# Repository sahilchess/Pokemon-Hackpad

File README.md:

# Pokemon Hackpad!
<!---

picture to come!
-->

[CAD](https://cad.onshape.com/documents/8d1a80880a531cce319d6767/w/a72820820093b362710dff01/e/ab70c80eedf68ce27917fcfd)

Pokemon Hackpad is a 5 key macropad with a rotary switch/encoder, and 4 SK6812 MINI E RGB LEDs. It uses KMK/QMK(wip) firmware. I designed this as my own macropad through [hackpad](https://hackclub.hackpad.com), a Hack Club program where you learn to design your own macropad and get it for free

## Features:
- An EC11 rotary encoder, controls volume, click to mute
- 3 SK6812 MINI E RGB LEDs, swirl and static modes
- 5 Cherry MX style keys
- 128x32 OLED Screen
- Pokemon themed design

## CAD Model:
Here is the case, made in onshape. I used onshape because Fusion basically blew my computer up. 

## PCB
Here's the PCB, made in KiCad.

## Firmware Overview
This hackpad uses [KMK](https://github.com/KMKfw/kmk_firmware) firmware for everything.
- the rotary encoder changes volume, press to mute
- the 5 regular keys are copy, paste, undo, redo
- rgb leds swirl by default, static color available

## BOM (more elaborate BOM [here](http://github.com/sahilchess/Pokemon-Hackpad/blob/main/production/BOM.md)):
Here should be everything you need to make this amazing hackpad
- 5x Cherry MX Switches
- 5x DSA Keycaps
- 6x 1N4148 DO-35 Diodes
- 3x SK6812 MINI E RGB LEDs
- 1x EC11 Rotary Encoder
- 1x 0.91 inch OLED display
- 4x M3x16mm screws
- 4x M3x5mx4mm heatset inserts
- 1x XIAO RP2040

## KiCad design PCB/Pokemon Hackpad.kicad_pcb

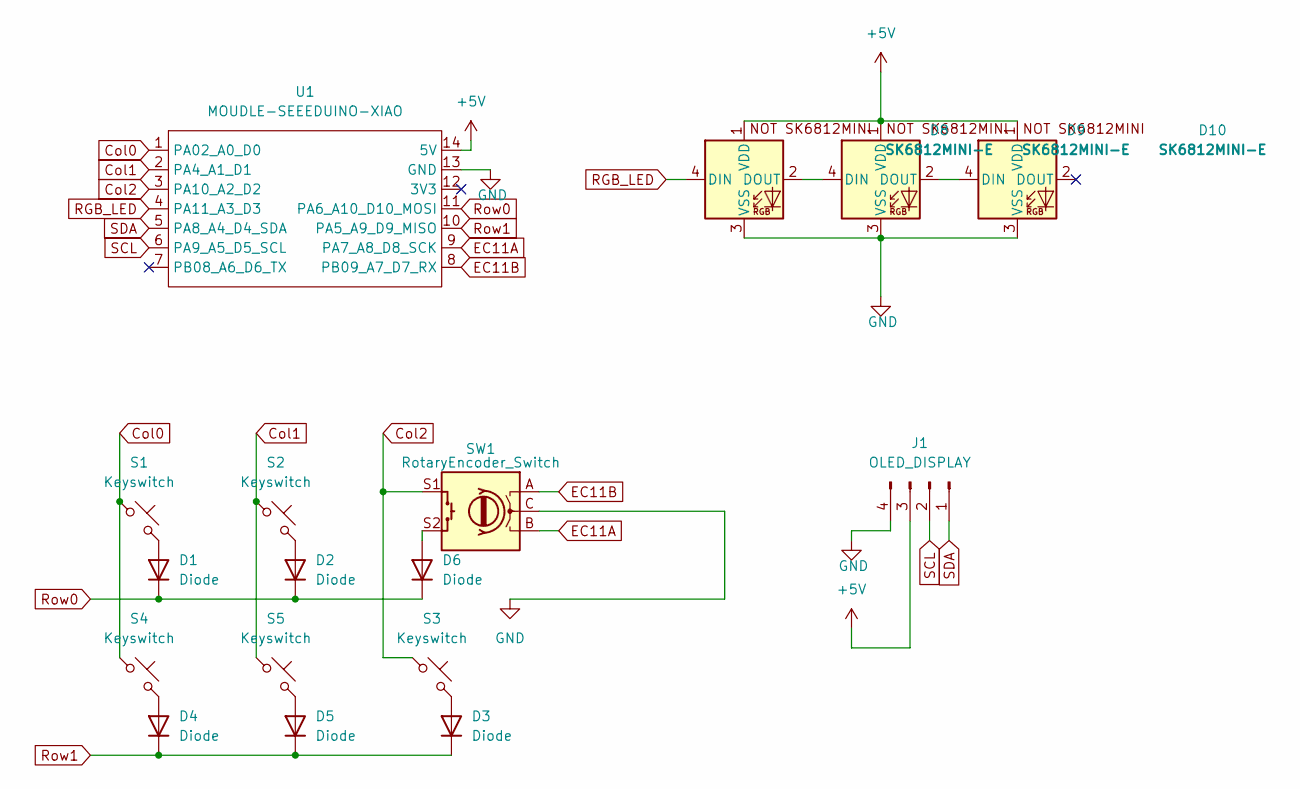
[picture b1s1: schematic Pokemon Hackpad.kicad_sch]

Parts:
D1, D2, D3, D4, D5, D6: Diode; D_DO-35_SOD27_P7.62mm_Horizontal
D8, D9, D10: SK6812MINI-E; LED_SK6812MINI-E_3.2x2.8mm_P1.5mm_ReverseMount
J1: OLED_DISPLAY; SSD1306-0.91-OLED-4pin-128x32
S1, S2, S3, S4, S5: Keyswitch; SW_Cherry_MX_1.00u_PCB
SW1: RotaryEncoder_Switch; RotaryEncoder_Alps_EC11E-Switch_Vertical_H20mm
U1: MOUDLE-SEEEDUINO-XIAO; XIAO-Generic-Hybrid-14P-2.54-21X17.8MM

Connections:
+5V: D8.1 (VDD), D9.1 (VDD), D10.1 (VDD), J1.3, U1.14 (5V)
Col0: S1.1, S4.1, U1.1 (PA02_A0_D0)
Col1: S2.1, S5.1, U1.2 (PA4_A1_D1)
Col2: S3.1, SW1.S1, U1.3 (PA10_A2_D2)
EC11A: SW1.B, U1.9 (PA7_A8_D8_SCK)
EC11B: SW1.A, U1.8 (PB09_A7_D7_RX)
GND: D8.3 (VSS), D9.3 (VSS), D10.3 (VSS), J1.4, SW1.C, U1.13 (GND)
unnamed: D1.2 (A), S1.2
unnamed: D2.2 (A), S2.2
unnamed: D3.2 (A), S3.2
unnamed: D4.2 (A), S4.2
unnamed: D5.2 (A), S5.2
unnamed: D6.2 (A), SW1.S2
unnamed: D8.2 (DOUT), D9.4 (DIN)
unnamed: D9.2 (DOUT), D10.4 (DIN)
RGB_LED: D8.4 (DIN), U1.4 (PA11_A3_D3)
Row0: D1.1 (K), D2.1 (K), D6.1 (K), U1.11 (PA6_A10_D10_MOSI)
Row1: D3.1 (K), D4.1 (K), D5.1 (K), U1.10 (PA5_A9_D9_MISO)
SCL: J1.2, U1.6 (PA9_A5_D5_SCL)
SDA: J1.1, U1.5 (PA8_A4_D4_SDA)

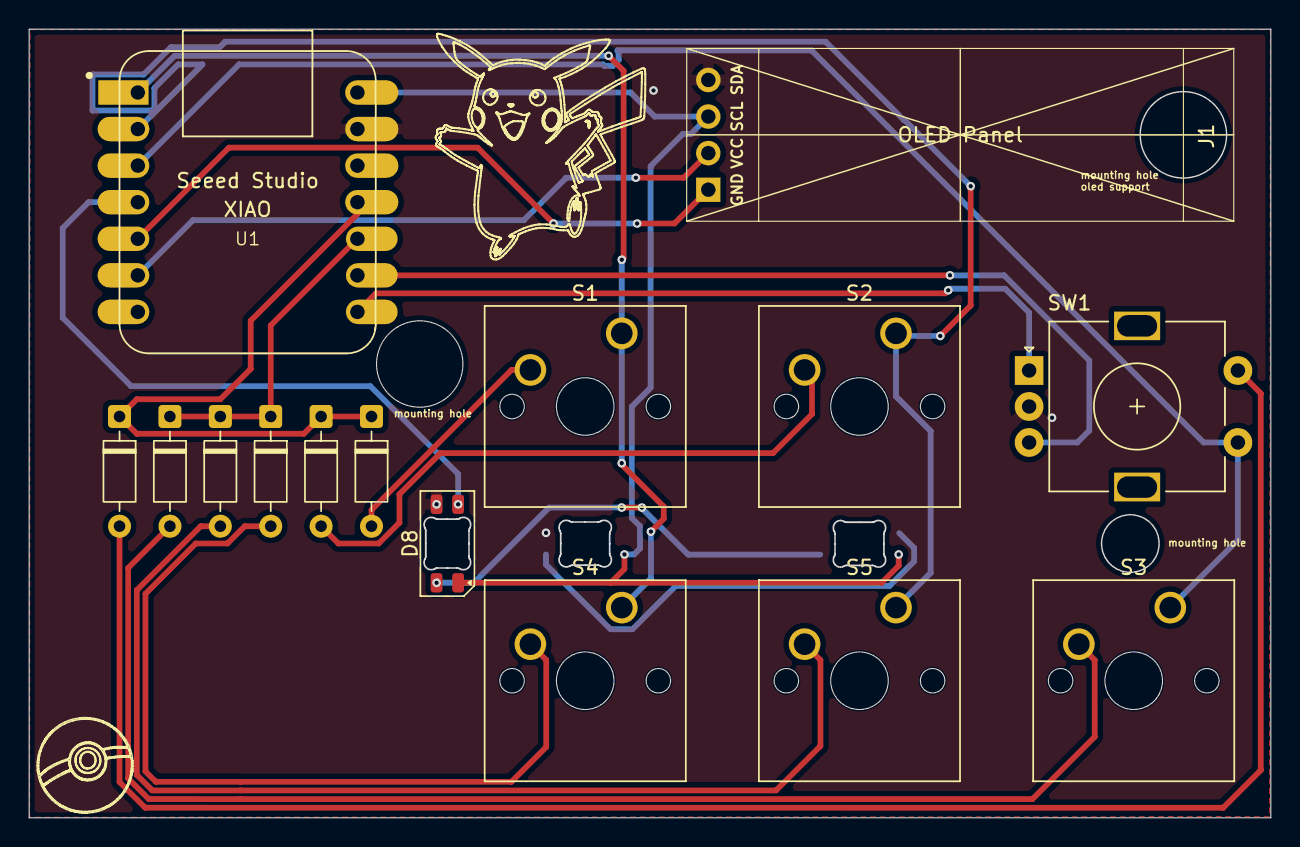
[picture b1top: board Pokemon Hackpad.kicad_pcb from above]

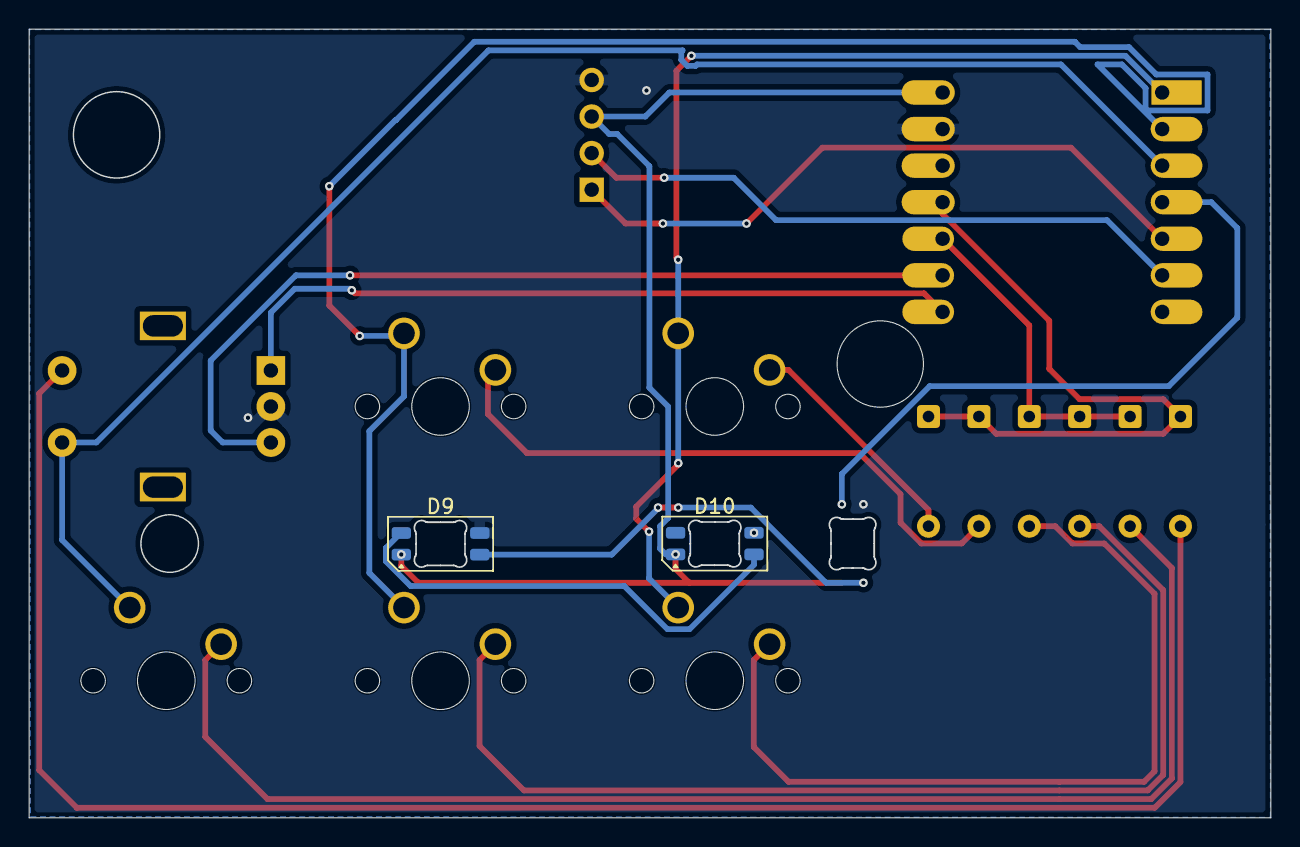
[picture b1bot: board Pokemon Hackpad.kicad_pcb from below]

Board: 2 copper layers, 86.2 x 54.8 mm, 17 parts (2 on the bottom side), 20 nets.

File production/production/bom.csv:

Designator,Footprint,Quantity,Value,LCSC Part #
"D1, D2, D3, D4, D5, D6",D_DO-35_SOD27_P7.62mm_Horizontal,6,Diode,
"D10, D7, D8, D9",LED_SK6812MINI-E_3.2x2.8mm_P1.5mm_ReverseMount,4,SK6812MINI-E,
"S1, S2, S3, S4, S5",SW_Cherry_MX_1.00u_PCB,5,Keyswitch,
SW1,RotaryEncoder_Alps_EC11E-Switch_Vertical_H20mm,1,RotaryEncoder_Switch,
U1,XIAO-Generic-Hybrid-14P-2.54-21X17.8MM,1,MOUDLE-SEEEDUINO-XIAO,

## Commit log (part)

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2026-06-19 init
2026-06-19 added rgb leds
2026-06-19 update to firmware
2026-06-20 submission file structure
2026-06-20 submission files
2026-06-20 Rename kicad_icon.png to icons/kicad_icon.png
2026-06-20 Rename onshape_icon.png to icons/onshape_icon.png
